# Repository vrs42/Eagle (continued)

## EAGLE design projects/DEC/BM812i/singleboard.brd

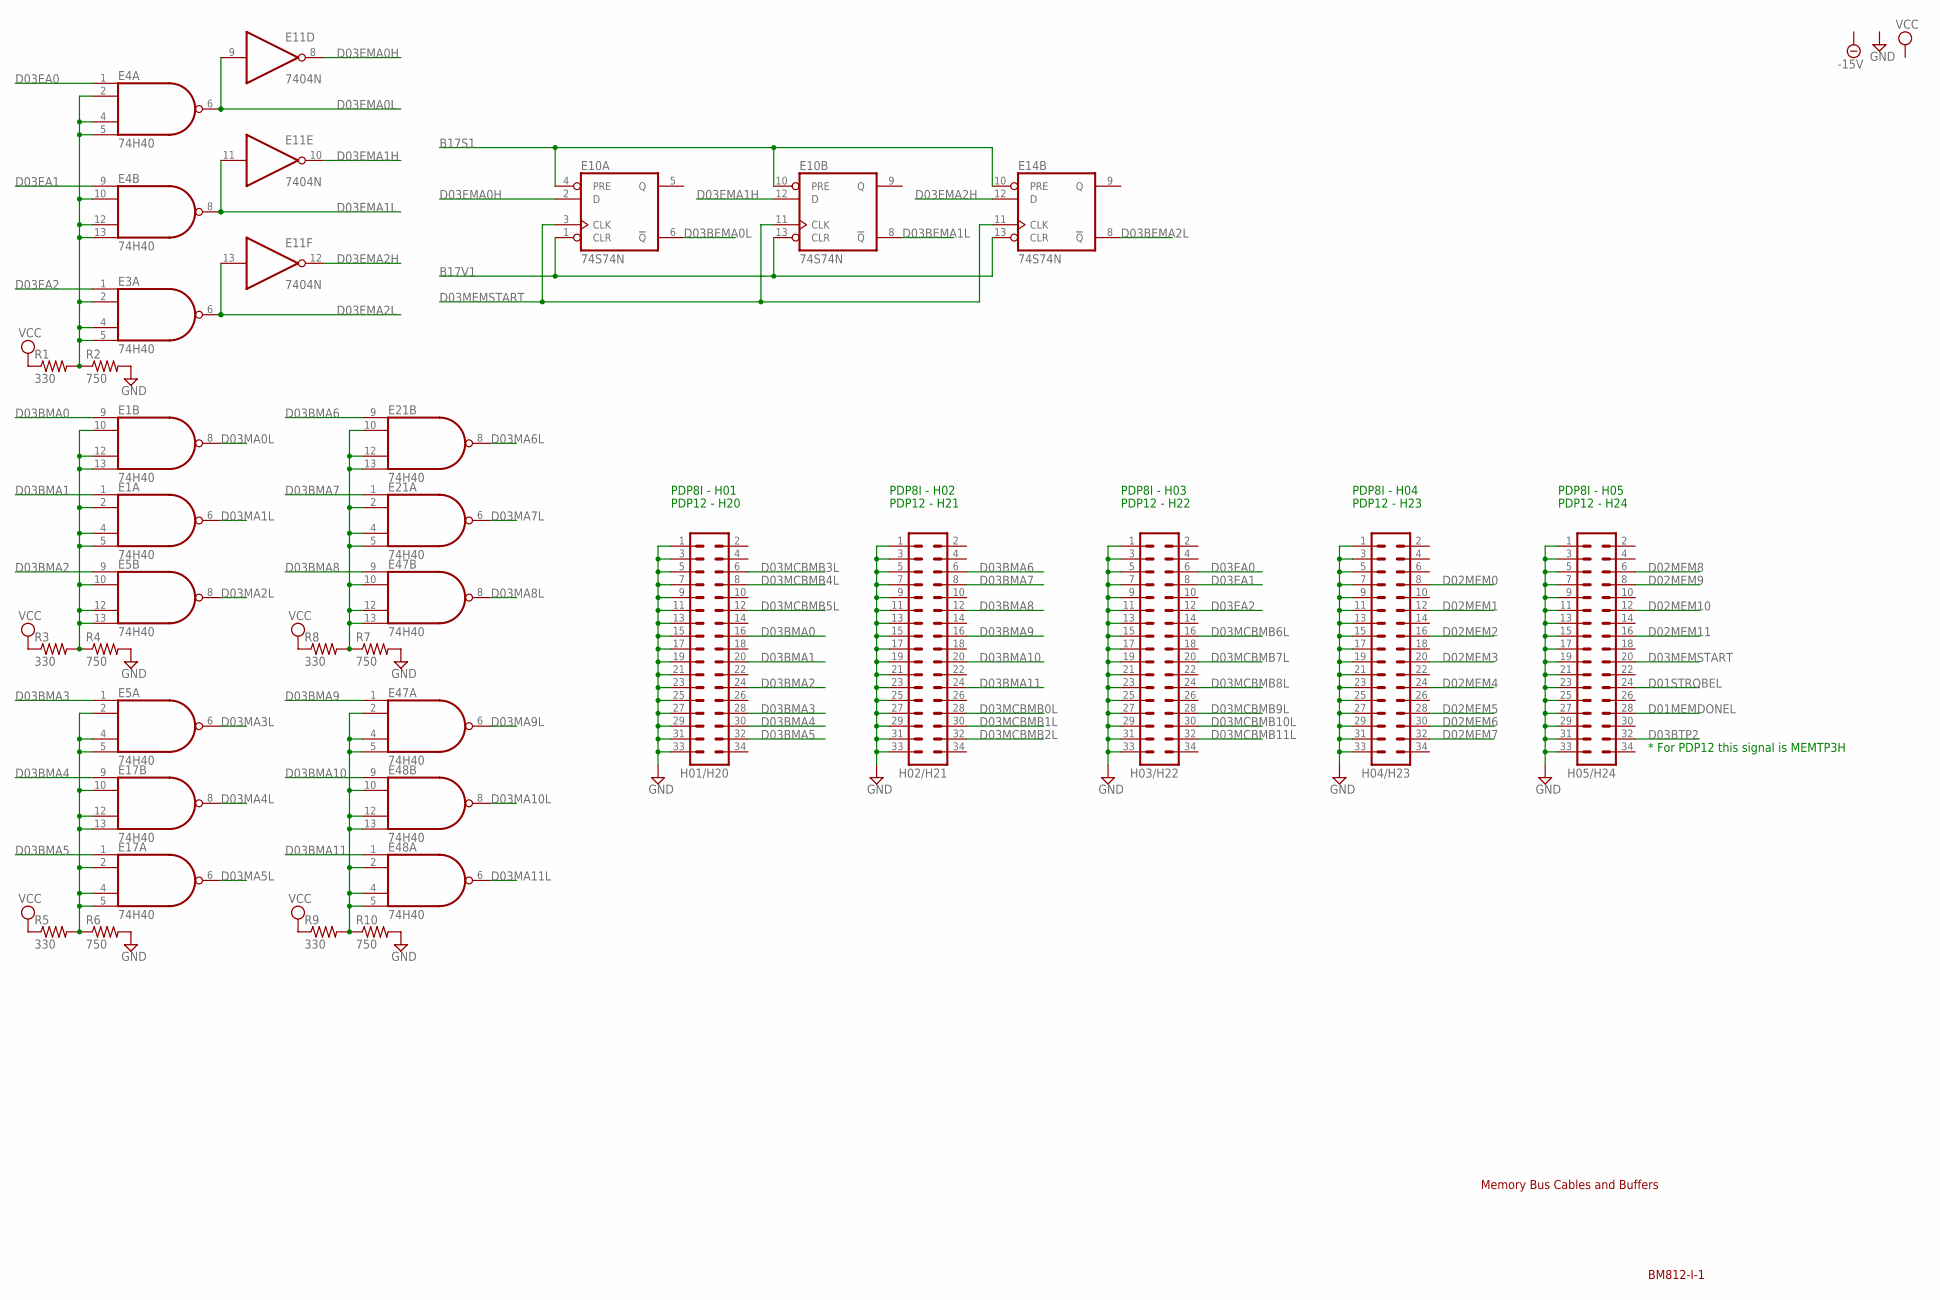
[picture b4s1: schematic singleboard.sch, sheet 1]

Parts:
E1, E3, E4, E5, E17, E21, E47, E48: 74H40; DIL14
E10, E14: 74S74N; DIL14
E11: 7404N; DIL14
H01/H20, H02/H21, H03/H22, H04/H23, H05/H24: MA17-2
R1, R3, R5, R8, R9: 330; 0207/10
R2, R4, R6, R7, R10: 750; 0207/10

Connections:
B17S1: E10.4 (PRE), E10.10 (PRE), E14.10 (PRE); also elsewhere on the board
B17V1: E10.1 (CLR), E10.13 (CLR), E14.13 (CLR); also elsewhere on the board
D01MEMDONEL: H05/H24.28; also elsewhere on the board
D01STROBEL: H05/H24.24; also elsewhere on the board
D02MEM0: H04/H23.8; also elsewhere on the board
D02MEM1: H04/H23.12; also elsewhere on the board
D02MEM2: H04/H23.16; also elsewhere on the board
D02MEM3: H04/H23.20; also elsewhere on the board
D02MEM4: H04/H23.24; also elsewhere on the board
D02MEM5: H04/H23.28; also elsewhere on the board
D02MEM6: H04/H23.30; also elsewhere on the board
D02MEM7: H04/H23.32; also elsewhere on the board
D02MEM8: H05/H24.6; also elsewhere on the board
D02MEM9: H05/H24.8; also elsewhere on the board
D02MEM10: H05/H24.12; also elsewhere on the board
D02MEM11: H05/H24.16; also elsewhere on the board
D03BEMA0L: E10.6 (!Q); also elsewhere on the board
D03BEMA1L: E10.8 (!Q); also elsewhere on the board
D03BEMA2L: E14.8 (!Q); also elsewhere on the board
D03BMA0: E1.9 (I0), H01/H20.16
D03BMA1: E1.1 (I0), H01/H20.20
D03BMA2: E5.9 (I0), H01/H20.24
D03BMA3: E5.1 (I0), H01/H20.28
D03BMA4: E17.9 (I0), H01/H20.30
D03BMA5: E17.1 (I0), H01/H20.32
D03BMA6: E21.9 (I0), H02/H21.6
D03BMA7: E21.1 (I0), H02/H21.8
D03BMA8: E47.9 (I0), H02/H21.12
D03BMA9: E47.1 (I0), H02/H21.16
D03BMA10: E48.9 (I0), H02/H21.20
D03BMA11: E48.1 (I0), H02/H21.24
D03BTP2: H05/H24.32; also elsewhere on the board
D03EA0: E4.1 (I0), H03/H22.6
D03EA1: E4.9 (I0), H03/H22.8
D03EA2: E3.1 (I0), H03/H22.12
D03EMA0H: E10.2 (D), E11.8 (O); also elsewhere on the board
D03EMA0L: E4.6 (O), E11.9 (I); also elsewhere on the board
D03EMA1H: E10.12 (D), E11.10 (O); also elsewhere on the board
D03EMA1L: E4.8 (O), E11.11 (I); also elsewhere on the board
D03EMA2H: E11.12 (O), E14.12 (D); also elsewhere on the board
D03EMA2L: E3.6 (O), E11.13 (I); also elsewhere on the board
D03MA0L: E1.8 (O); also elsewhere on the board
D03MA1L: E1.6 (O); also elsewhere on the board
D03MA2L: E5.8 (O); also elsewhere on the board
D03MA3L: E5.6 (O); also elsewhere on the board
D03MA4L: E17.8 (O); also elsewhere on the board
D03MA5L: E17.6 (O); also elsewhere on the board
D03MA6L: E21.8 (O); also elsewhere on the board
D03MA7L: E21.6 (O); also elsewhere on the board
D03MA8L: E47.8 (O); also elsewhere on the board
D03MA9L: E47.6 (O); also elsewhere on the board
D03MA10L: E48.8 (O); also elsewhere on the board
D03MA11L: E48.6 (O); also elsewhere on the board
D03MCBMB0L: H02/H21.28; also elsewhere on the board
D03MCBMB1L: H02/H21.30; also elsewhere on the board
D03MCBMB2L: H02/H21.32; also elsewhere on the board
D03MCBMB3L: H01/H20.6; also elsewhere on the board
D03MCBMB4L: H01/H20.8; also elsewhere on the board
D03MCBMB5L: H01/H20.12; also elsewhere on the board
D03MCBMB6L: H03/H22.16; also elsewhere on the board
D03MCBMB7L: H03/H22.20; also elsewhere on the board
D03MCBMB8L: H03/H22.24; also elsewhere on the board
D03MCBMB9L: H03/H22.28; also elsewhere on the board
D03MCBMB10L: H03/H22.30; also elsewhere on the board
D03MCBMB11L: H03/H22.32; also elsewhere on the board
D03MEMSTART: E10.3 (CLK), E10.11 (CLK), E14.11 (CLK), H05/H24.20; also elsewhere on the board
GND: E1.7 (GND), E3.7 (GND), E4.7 (GND), E5.7 (GND), E10.7 (GND), E11.7 (GND), E14.7 (GND), E17.7 (GND), E21.7 (GND), E47.7 (GND), E48.7 (GND), H01/H20.1, H01/H20.3, H01/H20.5, H01/H20.7, H01/H20.9, H01/H20.11, H01/H20.13, H01/H20.15, H01/H20.17, H01/H20.19, H01/H20.21, H01/H20.23, H01/H20.25, H01/H20.27, H01/H20.29, H01/H20.31, H01/H20.33, H02/H21.1, H02/H21.3, H02/H21.5, H02/H21.7, H02/H21.9, H02/H21.11, H02/H21.13, H02/H21.15, H02/H21.17, H02/H21.19, H02/H21.21, H02/H21.23, H02/H21.25, H02/H21.27, H02/H21.29, H02/H21.31, H02/H21.33, H03/H22.1, H03/H22.3, H03/H22.5, H03/H22.7, H03/H22.9, H03/H22.11, H03/H22.13, H03/H22.15, H03/H22.17, H03/H22.19, H03/H22.21, H03/H22.23, H03/H22.25, H03/H22.27, H03/H22.29, H03/H22.31, H03/H22.33, H04/H23.1, H04/H23.3, H04/H23.5, H04/H23.7, H04/H23.9, H04/H23.11, H04/H23.13, H04/H23.15, H04/H23.17, H04/H23.19, H04/H23.21, H04/H23.23, H04/H23.25, H04/H23.27, H04/H23.29, H04/H23.31, H04/H23.33, H05/H24.1, H05/H24.3, H05/H24.5, H05/H24.7, H05/H24.9, H05/H24.11, H05/H24.13, H05/H24.15, H05/H24.17, H05/H24.19, H05/H24.21, H05/H24.23, H05/H24.25, H05/H24.27, H05/H24.29, H05/H24.31, H05/H24.33, R2.2, R4.2, R6.2, R7.2, R10.2; also elsewhere on the board
unnamed: E3.2 (I1), E3.4 (I2), E3.5 (I3), E4.2 (I1), E4.4 (I2), E4.5 (I3), E4.10 (I1), E4.12 (I2), E4.13 (I3), R1.2, R2.1
unnamed: E1.2 (I1), E1.4 (I2), E1.5 (I3), E1.10 (I1), E1.12 (I2), E1.13 (I3), E5.10 (I1), E5.12 (I2), E5.13 (I3), R3.2, R4.1
unnamed: E5.2 (I1), E5.4 (I2), E5.5 (I3), E17.2 (I1), E17.4 (I2), E17.5 (I3), E17.10 (I1), E17.12 (I2), E17.13 (I3), R5.2, R6.1
unnamed: E21.2 (I1), E21.4 (I2), E21.5 (I3), E21.10 (I1), E21.12 (I2), E21.13 (I3), E47.10 (I1), E47.12 (I2), E47.13 (I3), R7.1, R8.2
unnamed: E47.2 (I1), E47.4 (I2), E47.5 (I3), E48.2 (I1), E48.4 (I2), E48.5 (I3), E48.10 (I1), E48.12 (I2), E48.13 (I3), R9.2, R10.1
VCC: E1.14 (VCC), E3.14 (VCC), E4.14 (VCC), E5.14 (VCC), E10.14 (VCC), E11.14 (VCC), E14.14 (VCC), E17.14 (VCC), E21.14 (VCC), E47.14 (VCC), E48.14 (VCC), R1.1, R3.1, R5.1, R8.1, R9.1; also elsewhere on the board

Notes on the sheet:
Memory Bus Cables and Buffers
BM812-I-1
* For PDP12 this signal is MEMTP3H
PDP8I - H01
PDP8I - H02
PDP8I - H03
PDP8I - H04
PDP8I - H05
PDP12 - H20
PDP12 - H21
PDP12 - H22
PDP12 - H23
PDP12 - H24

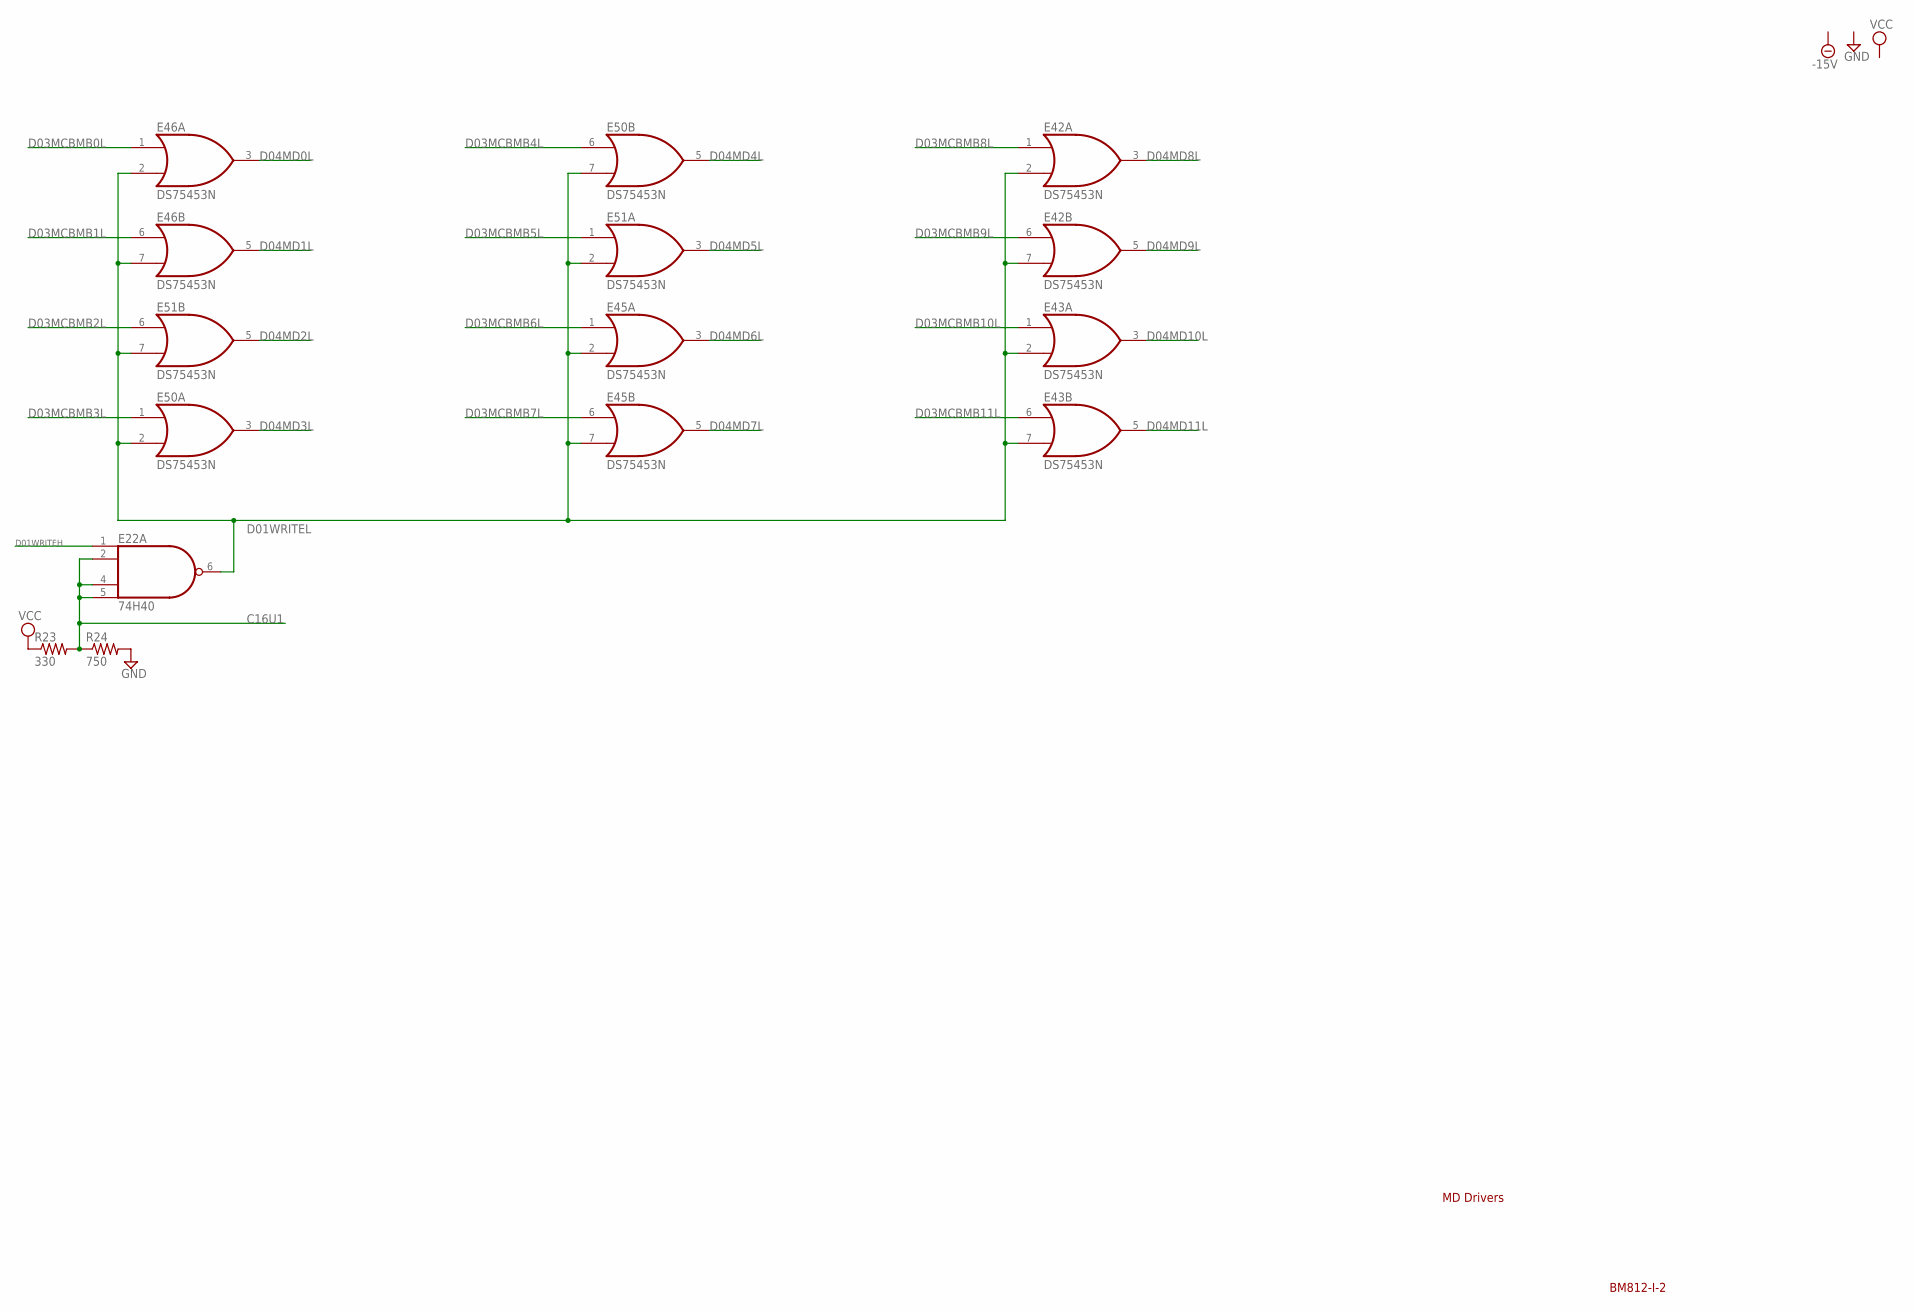
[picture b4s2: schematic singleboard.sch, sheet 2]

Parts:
E22: 74H40; DIL14
E42, E43, E45, E46, E50, E51: DS75453N; DIL08
R23: 330; 0207/10
R24: 750; 0207/10

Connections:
C16U1: E22.2 (I1), E22.4 (I2), E22.5 (I3), R23.2, R24.1; also elsewhere on the board
D01WRITEH: E22.1 (I0); also elsewhere on the board
D01WRITEL: E22.6 (O), E42.2 (I1), E42.7 (I1), E43.2 (I1), E43.7 (I1), E45.2 (I1), E45.7 (I1), E46.2 (I1), E46.7 (I1), E50.2 (I1), E50.7 (I1), E51.2 (I1), E51.7 (I1)
D03MCBMB0L: E46.1 (I0); also elsewhere on the board
D03MCBMB1L: E46.6 (I0); also elsewhere on the board
D03MCBMB2L: E51.6 (I0); also elsewhere on the board
D03MCBMB3L: E50.1 (I0); also elsewhere on the board
D03MCBMB4L: E50.6 (I0); also elsewhere on the board
D03MCBMB5L: E51.1 (I0); also elsewhere on the board
D03MCBMB6L: E45.1 (I0); also elsewhere on the board
D03MCBMB7L: E45.6 (I0); also elsewhere on the board
D03MCBMB8L: E42.1 (I0); also elsewhere on the board
D03MCBMB9L: E42.6 (I0); also elsewhere on the board
D03MCBMB10L: E43.1 (I0); also elsewhere on the board
D03MCBMB11L: E43.6 (I0); also elsewhere on the board
D04MD0L: E46.3 (O); also elsewhere on the board
D04MD1L: E46.5 (O); also elsewhere on the board
D04MD2L: E51.5 (O); also elsewhere on the board
D04MD3L: E50.3 (O); also elsewhere on the board
D04MD4L: E50.5 (O); also elsewhere on the board
D04MD5L: E51.3 (O); also elsewhere on the board
D04MD6L: E45.3 (O); also elsewhere on the board
D04MD7L: E45.5 (O); also elsewhere on the board
D04MD8L: E42.3 (O); also elsewhere on the board
D04MD9L: E42.5 (O); also elsewhere on the board
D04MD10L: E43.3 (O); also elsewhere on the board
D04MD11L: E43.5 (O); also elsewhere on the board
GND: E22.7 (GND), E42.4 (GND), E43.4 (GND), E45.4 (GND), E46.4 (GND), E50.4 (GND), E51.4 (GND), R24.2; also elsewhere on the board
VCC: E22.14 (VCC), E42.8 (VCC), E43.8 (VCC), E45.8 (VCC), E46.8 (VCC), E50.8 (VCC), E51.8 (VCC), R23.1; also elsewhere on the board

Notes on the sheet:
BM812-I-2
MD Drivers

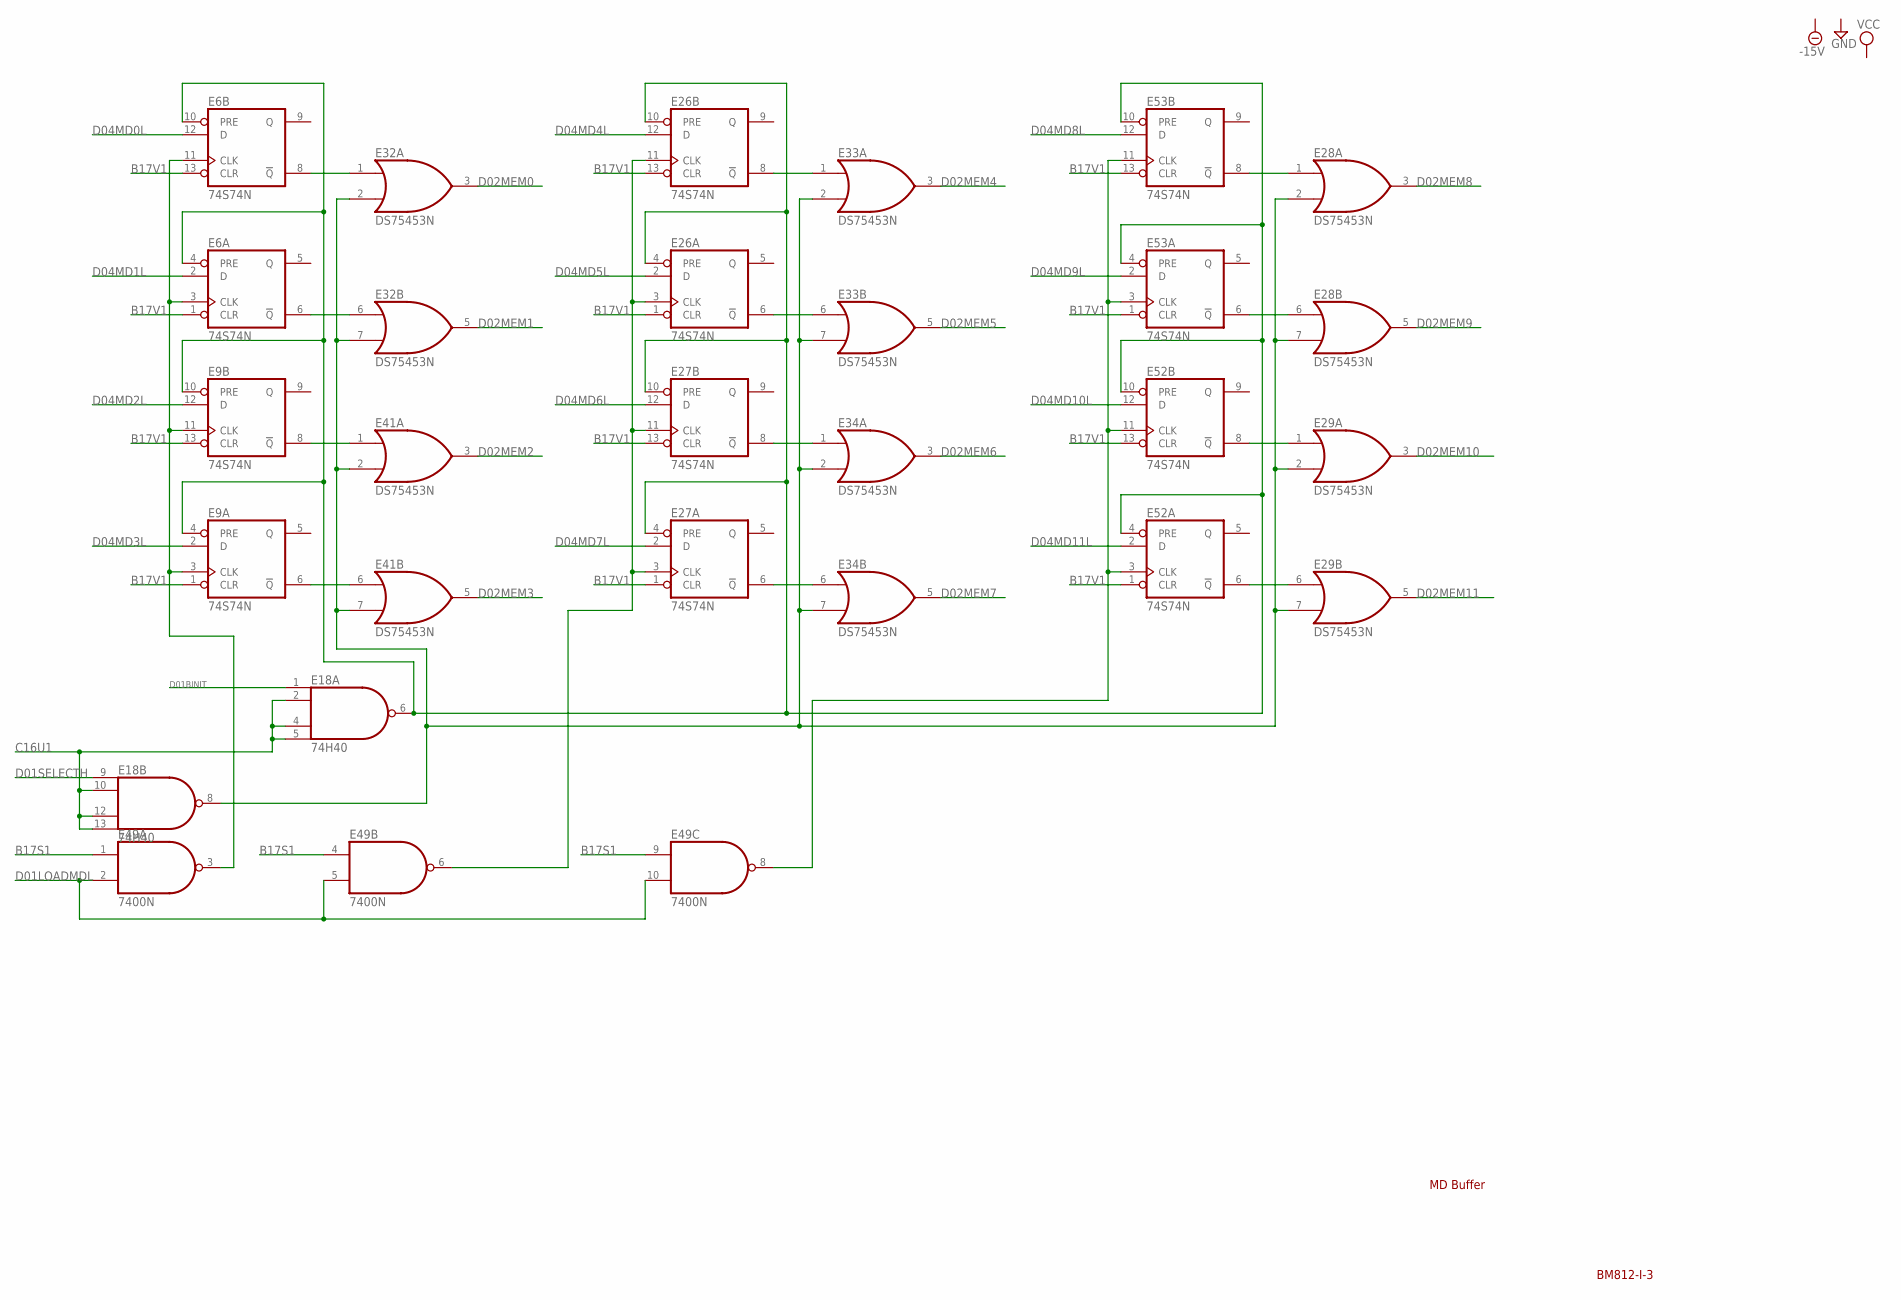
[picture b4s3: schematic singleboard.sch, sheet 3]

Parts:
E6, E9, E26, E27, E52, E53: 74S74N; DIL14
E18: 74H40; DIL14
E28, E29, E32, E33, E34, E41: DS75453N; DIL08
E49: 7400N; DIL14

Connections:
B17S1: E49.1 (I0), E49.4 (I0), E49.9 (I0); also elsewhere on the board
B17V1: E6.1 (CLR), E6.13 (CLR), E9.1 (CLR), E9.13 (CLR), E26.1 (CLR), E26.13 (CLR), E27.1 (CLR), E27.13 (CLR), E52.1 (CLR), E52.13 (CLR), E53.1 (CLR), E53.13 (CLR); also elsewhere on the board
C16U1: E18.2 (I1), E18.4 (I2), E18.5 (I3), E18.10 (I1), E18.12 (I2), E18.13 (I3); also elsewhere on the board
D01BINIT: E18.1 (I0); also elsewhere on the board
D01LOADMDL: E49.2 (I1), E49.5 (I1), E49.10 (I1); also elsewhere on the board
D01SELECTH: E18.9 (I0); also elsewhere on the board
D02MEM0: E32.3 (O); also elsewhere on the board
D02MEM1: E32.5 (O); also elsewhere on the board
D02MEM2: E41.3 (O); also elsewhere on the board
D02MEM3: E41.5 (O); also elsewhere on the board
D02MEM4: E33.3 (O); also elsewhere on the board
D02MEM5: E33.5 (O); also elsewhere on the board
D02MEM6: E34.3 (O); also elsewhere on the board
D02MEM7: E34.5 (O); also elsewhere on the board
D02MEM8: E28.3 (O); also elsewhere on the board
D02MEM9: E28.5 (O); also elsewhere on the board
D02MEM10: E29.3 (O); also elsewhere on the board
D02MEM11: E29.5 (O); also elsewhere on the board
D04MD0L: E6.12 (D); also elsewhere on the board
D04MD1L: E6.2 (D); also elsewhere on the board
D04MD2L: E9.12 (D); also elsewhere on the board
D04MD3L: E9.2 (D); also elsewhere on the board
D04MD4L: E26.12 (D); also elsewhere on the board
D04MD5L: E26.2 (D); also elsewhere on the board
D04MD6L: E27.12 (D); also elsewhere on the board
D04MD7L: E27.2 (D); also elsewhere on the board
D04MD8L: E53.12 (D); also elsewhere on the board
D04MD9L: E53.2 (D); also elsewhere on the board
D04MD10L: E52.12 (D); also elsewhere on the board
D04MD11L: E52.2 (D); also elsewhere on the board
GND: E6.7 (GND), E9.7 (GND), E18.7 (GND), E26.7 (GND), E27.7 (GND), E28.4 (GND), E29.4 (GND), E32.4 (GND), E33.4 (GND), E34.4 (GND), E41.4 (GND), E49.7 (GND), E52.7 (GND), E53.7 (GND); also elsewhere on the board
unnamed: E6.3 (CLK), E6.11 (CLK), E9.3 (CLK), E9.11 (CLK), E49.3 (O)
unnamed: E9.6 (!Q), E41.6 (I0)
unnamed: E6.8 (!Q), E32.1 (I0)
unnamed: E6.6 (!Q), E32.6 (I0)
unnamed: E26.3 (CLK), E26.11 (CLK), E27.3 (CLK), E27.11 (CLK), E49.6 (O)
unnamed: E9.8 (!Q), E41.1 (I0)
unnamed: E6.4 (PRE), E6.10 (PRE), E9.4 (PRE), E9.10 (PRE), E18.6 (O), E26.4 (PRE), E26.10 (PRE), E27.4 (PRE), E27.10 (PRE), E52.4 (PRE), E52.10 (PRE), E53.4 (PRE), E53.10 (PRE)
unnamed: E18.8 (O), E28.2 (I1), E28.7 (I1), E29.2 (I1), E29.7 (I1), E32.2 (I1), E32.7 (I1), E33.2 (I1), E33.7 (I1), E34.2 (I1), E34.7 (I1), E41.2 (I1), E41.7 (I1)
unnamed: E26.6 (!Q), E33.6 (I0)
unnamed: E27.6 (!Q), E34.6 (I0)
unnamed: E27.8 (!Q), E34.1 (I0)
unnamed: E26.8 (!Q), E33.1 (I0)
unnamed: E29.6 (I0), E52.6 (!Q)
unnamed: E29.1 (I0), E52.8 (!Q)
unnamed: E49.8 (O), E52.3 (CLK), E52.11 (CLK), E53.3 (CLK), E53.11 (CLK)
unnamed: E28.6 (I0), E53.6 (!Q)
unnamed: E28.1 (I0), E53.8 (!Q)
VCC: E6.14 (VCC), E9.14 (VCC), E18.14 (VCC), E26.14 (VCC), E27.14 (VCC), E28.8 (VCC), E29.8 (VCC), E32.8 (VCC), E33.8 (VCC), E34.8 (VCC), E41.8 (VCC), E49.14 (VCC), E52.14 (VCC), E53.14 (VCC); also elsewhere on the board

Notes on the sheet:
MD Buffer
BM812-I-3

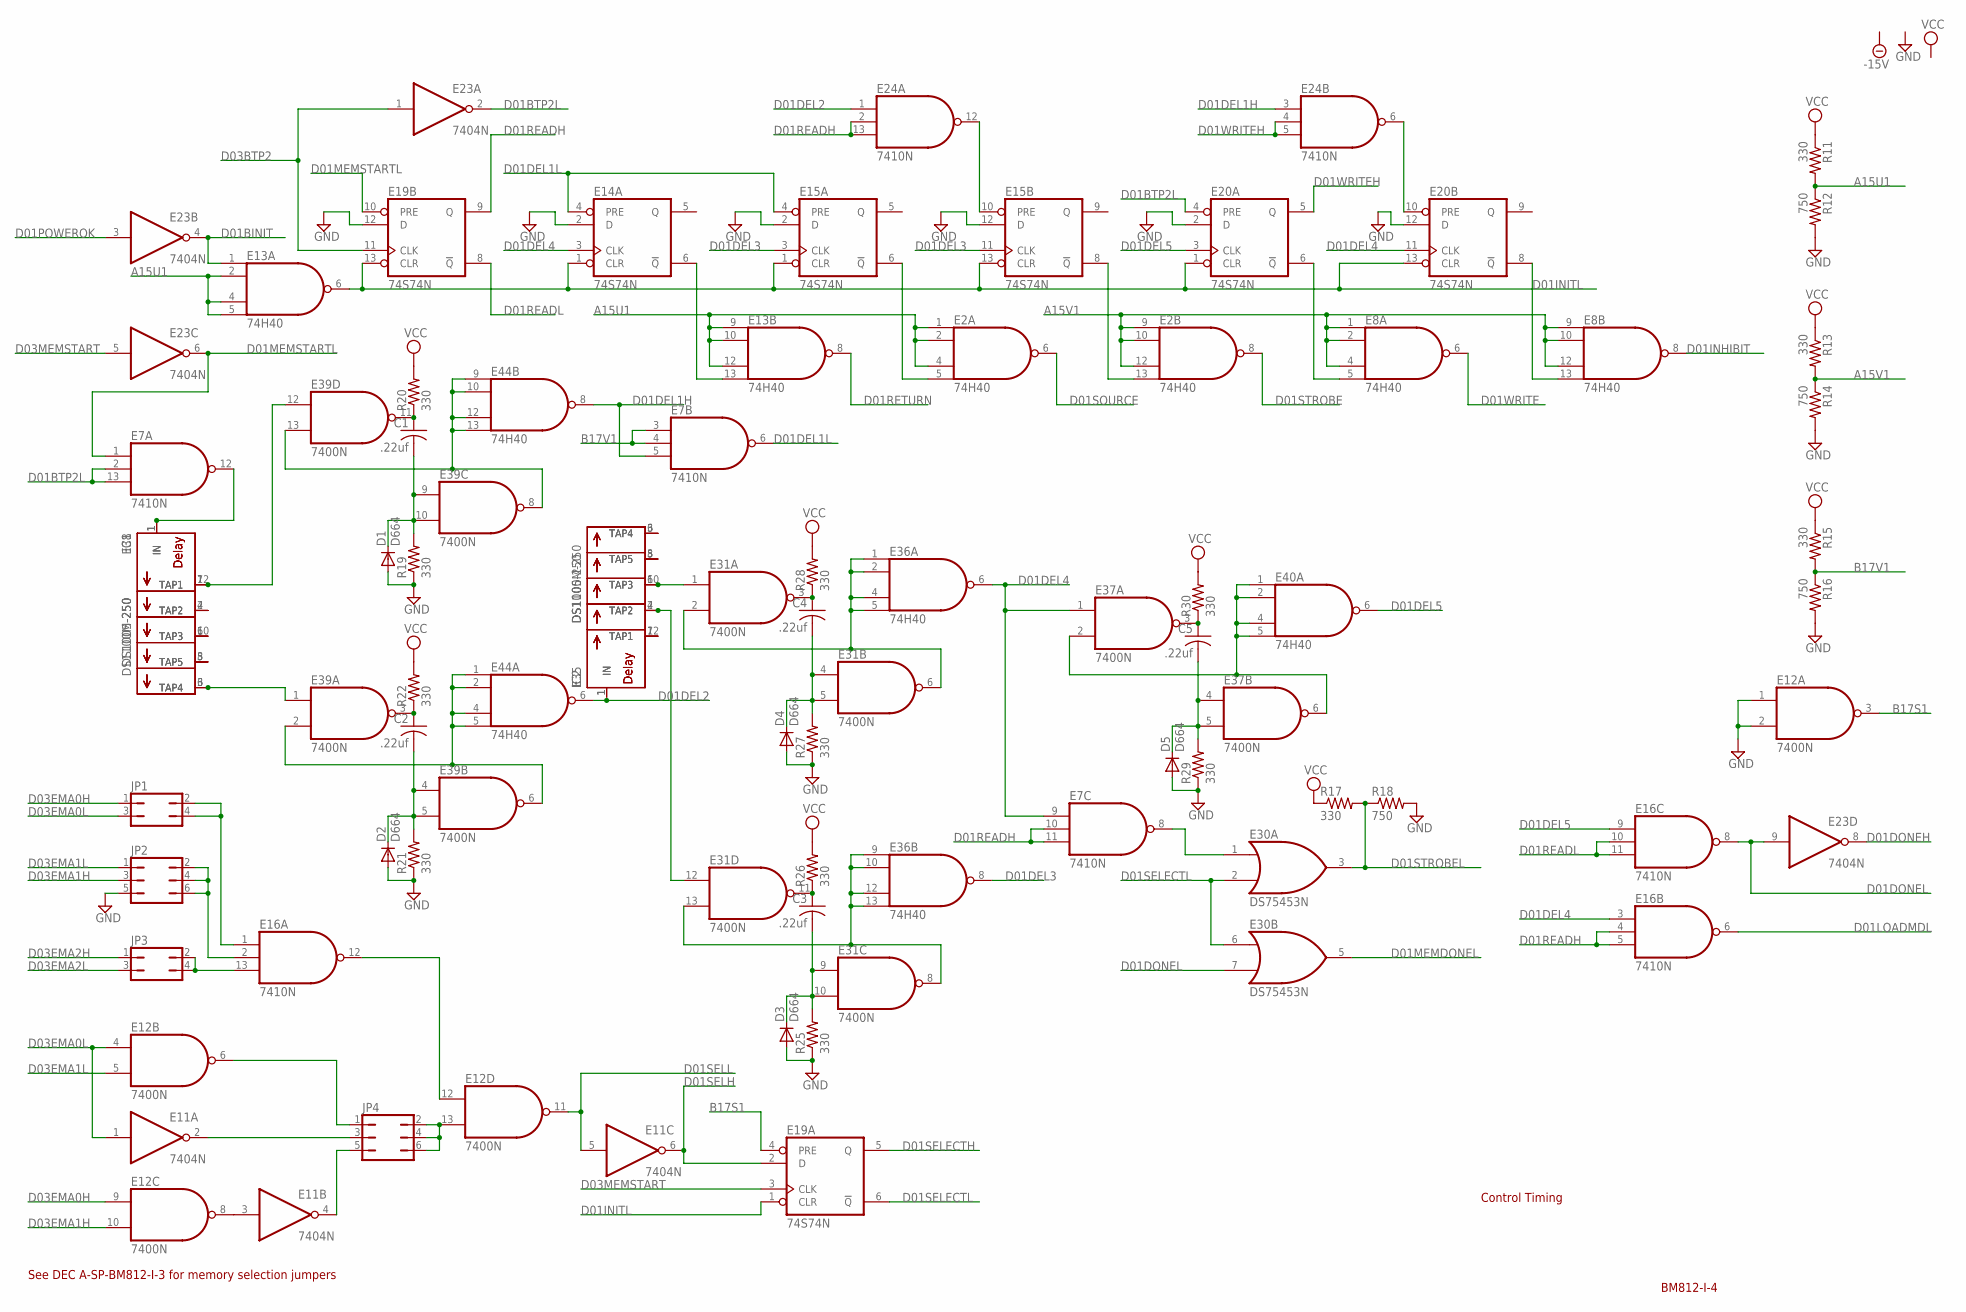
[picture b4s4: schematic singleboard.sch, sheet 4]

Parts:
C1, C2, C3, C4, C5: .22uf; C050-025X075
D1, D2, D3, D4, D5: D664; DO35-10
E2, E8, E13, E36, E40, E44: 74H40; DIL14
E7, E16, E24: 7410N; DIL14
E11, E23: 7404N; DIL14
E12, E31, E37, E39: 7400N; DIL14
E14, E15, E19, E20: 74S74N; DIL14
E30: DS75453N; DIL08
E35, E38: DS1005-250; DIL14
IC1, IC2: DS1100M-250; DIL08
JP1, JP3: JP2Q
JP2, JP4: JP3Q
R11, R13, R15, R17, R19, R20, R21, R22, R25, R26, R27, R28, R29, R30: 330; 0207/10
R12, R14, R16, R18: 750; 0207/10

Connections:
A15U1: E2.1 (I0), E2.2 (I1), E2.4 (I2), E13.2 (I1), E13.4 (I2), E13.5 (I3), E13.9 (I0), E13.10 (I1), E13.12 (I2), R11.2, R12.1; also elsewhere on the board
A15V1: E2.9 (I0), E2.10 (I1), E2.12 (I2), E8.1 (I0), E8.2 (I1), E8.4 (I2), E8.9 (I0), E8.10 (I1), E8.12 (I2), R13.2, R14.1
B17S1: E12.3 (O), E19.4 (PRE); also elsewhere on the board
B17V1: E7.3 (I0), E7.4 (I1), R15.2, R16.1; also elsewhere on the board
D01BINIT: E13.1 (I0), E23.4 (O); also elsewhere on the board
D01BTP2L: E7.2 (I1), E7.13 (I2), E20.4 (PRE), E23.2 (O)
D01DEL1H: E7.5 (I2), E24.3 (I0), E44.8 (O)
D01DEL1L: E7.6 (O), E14.4 (PRE), E15.4 (PRE)
D01DEL2: E24.1 (I0), E35.1 (IN), E44.6 (O), IC2.1 (IN)
D01DEL3: E15.3 (CLK), E15.11 (CLK), E36.8 (O)
D01DEL4: E7.9 (I0), E14.3 (CLK), E16.3 (I0), E20.11 (CLK), E36.6 (O), E37.1 (I0)
D01DEL5: E16.9 (I0), E20.3 (CLK), E40.6 (O)
D01DONEH: E23.8 (O); also elsewhere on the board
D01DONEL: E16.8 (O), E23.9 (I), E30.7 (I1)
D01INHIBIT: E8.8 (O); also elsewhere on the board
D01INITL: E13.6 (O), E14.1 (CLR), E15.1 (CLR), E15.13 (CLR), E19.1 (CLR), E19.13 (CLR), E20.1 (CLR), E20.13 (CLR)
D01LOADMDL: E16.6 (O); also elsewhere on the board
D01MEMDONEL: E30.5 (O); also elsewhere on the board
D01MEMSTARTL: E7.1 (I0), E19.10 (PRE), E23.6 (O)
D01POWEROK: E23.3 (I); also elsewhere on the board
D01READH: E7.10 (I1), E7.11 (I2), E16.4 (I1), E16.5 (I2), E19.9 (Q), E24.2 (I1), E24.13 (I2)
D01READL: E16.10 (I1), E16.11 (I2), E19.8 (!Q); also elsewhere on the board
D01RETURN: E13.8 (O); also elsewhere on the board
D01SELECTH: E19.5 (Q); also elsewhere on the board
D01SELECTL: E19.6 (!Q), E30.2 (I1), E30.6 (I0)
D01SELH: E11.6 (O), E19.2 (D)
D01SELL: E11.5 (I), E12.11 (O)
D01SOURCE: E2.6 (O); also elsewhere on the board
D01STROBE: E2.8 (O); also elsewhere on the board
D01STROBEL: E30.3 (O), R17.2, R18.1; also elsewhere on the board
D01WRITE: E8.6 (O); also elsewhere on the board
D01WRITEH: E20.5 (Q), E24.4 (I1), E24.5 (I2); also elsewhere on the board
D03BTP2: E19.11 (CLK), E23.1 (I); also elsewhere on the board
D03EMA0H: E12.9 (I0), JP1.1; also elsewhere on the board
D03EMA0L: E11.1 (I), E12.4 (I0), JP1.3; also elsewhere on the board
D03EMA1H: E12.10 (I1), JP2.3; also elsewhere on the board
D03EMA1L: E12.5 (I1), JP2.1; also elsewhere on the board
D03EMA2H: JP3.1; also elsewhere on the board
D03EMA2L: JP3.3; also elsewhere on the board
D03MEMSTART: E19.3 (CLK), E23.5 (I); also elsewhere on the board
GND: D1.A, D2.A, D3.A, D4.A, D5.A, E2.7 (GND), E7.7 (GND), E8.7 (GND), E11.7 (GND), E12.1 (I0), E12.2 (I1), E12.7 (GND), E13.7 (GND), E14.2 (D), E14.7 (GND), E15.2 (D), E15.7 (GND), E15.12 (D), E16.7 (GND), E19.7 (GND), E19.12 (D), E20.2 (D), E20.7 (GND), E20.12 (D), E23.7 (GND), E24.7 (GND), E30.4 (GND), E31.7 (GND), E35.7 (GND), E36.7 (GND), E37.7 (GND), E38.7 (GND), E39.7 (GND), E40.7 (GND), E44.7 (GND), IC1.4 (GND), IC2.4 (GND), JP2.5, R12.2, R14.2, R16.2, R18.2, R19.1, R21.1, R25.1, R27.1, R29.1; also elsewhere on the board
unnamed: C3.2, D3.C, E31.9 (I0), E31.10 (I1), R25.2
unnamed: C5.2, D5.C, E37.4 (I0), E37.5 (I1), R29.2
unnamed: E12.13 (I1), JP4.2, JP4.4, JP4.6
unnamed: C2.2, D2.C, E39.4 (I0), E39.5 (I1), R21.2
unnamed: E38.12 (TAP1), E39.12 (I0), IC1.7 (TAP1)
unnamed: E31.12 (I0), E35.4 (TAP2), IC2.2 (TAP2)
unnamed: C1.2, D1.C, E39.9 (I0), E39.10 (I1), R19.2
unnamed: E39.8 (O), E39.13 (I1), E44.9 (I0), E44.10 (I1), E44.12 (I2), E44.13 (I3)
unnamed: C1.1, E39.11 (O), R20.1
unnamed: C2.1, E39.3 (O), R22.1
unnamed: E39.2 (I1), E39.6 (O), E44.1 (I0), E44.2 (I1), E44.4 (I2), E44.5 (I3)
unnamed: C3.1, E31.11 (O), R26.1
unnamed: E38.6 (TAP4), E39.1 (I0), IC1.3 (TAP4)
unnamed: E31.8 (O), E31.13 (I1), E36.9 (I0), E36.10 (I1), E36.12 (I2), E36.13 (I3)
unnamed: C4.2, D4.C, E31.4 (I0), E31.5 (I1), R27.2
unnamed: C4.1, E31.3 (O), R28.1
unnamed: E7.12 (O), E38.1 (IN), IC1.1 (IN)
unnamed: E31.2 (I1), E31.6 (O), E36.1 (I0), E36.2 (I1), E36.4 (I2), E36.5 (I3)
unnamed: E31.1 (I0), E35.10 (TAP3), IC2.6 (TAP3)
unnamed: C5.1, E37.3 (O), R30.1
unnamed: E37.2 (I1), E37.6 (O), E40.1 (I0), E40.2 (I1), E40.4 (I2), E40.5 (I3)
unnamed: E15.10 (PRE), E24.12 (O)
unnamed: E35.12 (TAP1), IC2.7 (TAP1)
unnamed: E35.6 (TAP4), IC2.3 (TAP4)
unnamed: E35.8 (TAP5), IC2.5 (TAP5)
unnamed: E38.4 (TAP2), IC1.2 (TAP2)
unnamed: E38.10 (TAP3), IC1.6 (TAP3)
unnamed: E38.8 (TAP5), IC1.5 (TAP5)
unnamed: E12.6 (O), JP4.1
unnamed: E20.10 (PRE), E24.6 (O)
unnamed: E7.8 (O), E30.1 (I0)
unnamed: E13.13 (I3), E14.6 (!Q)
unnamed: E2.5 (I3), E15.6 (!Q)
unnamed: E2.13 (I3), E15.8 (!Q)
unnamed: E11.2 (O), JP4.3
unnamed: E8.5 (I3), E20.6 (!Q)
unnamed: E11.3 (I), E12.8 (O)
unnamed: E8.13 (I3), E20.8 (!Q)
unnamed: E11.4 (O), JP4.5
unnamed: E16.13 (I2), JP3.2, JP3.4
unnamed: E16.2 (I1), JP2.2, JP2.4, JP2.6
unnamed: E16.1 (I0), JP1.2, JP1.4
unnamed: E12.12 (I0), E16.12 (O)
VCC: E2.14 (VCC), E7.14 (VCC), E8.14 (VCC), E11.14 (VCC), E12.14 (VCC), E13.14 (VCC), E14.14 (VCC), E15.14 (VCC), E16.14 (VCC), E19.14 (VCC), E20.14 (VCC), E23.14 (VCC), E24.14 (VCC), E30.8 (VCC), E31.14 (VCC), E35.14 (VCC), E36.14 (VCC), E37.14 (VCC), E38.14 (VCC), E39.14 (VCC), E40.14 (VCC), E44.14 (VCC), IC1.8 (VCC), IC2.8 (VCC), R11.1, R13.1, R15.1, R17.1, R20.2, R22.2, R26.2, R28.2, R30.2; also elsewhere on the board

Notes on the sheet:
BM812-I-4
Control Timing
See DEC A-SP-BM812-I-3 for memory selection jumpers
